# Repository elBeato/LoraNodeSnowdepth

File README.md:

# LoraNodeSnowdepth
A Sensor which measure the snowlevel, temperature and the humiditiy. The sensor is build as a Lora node and communicate over LoraLan with an gateway.

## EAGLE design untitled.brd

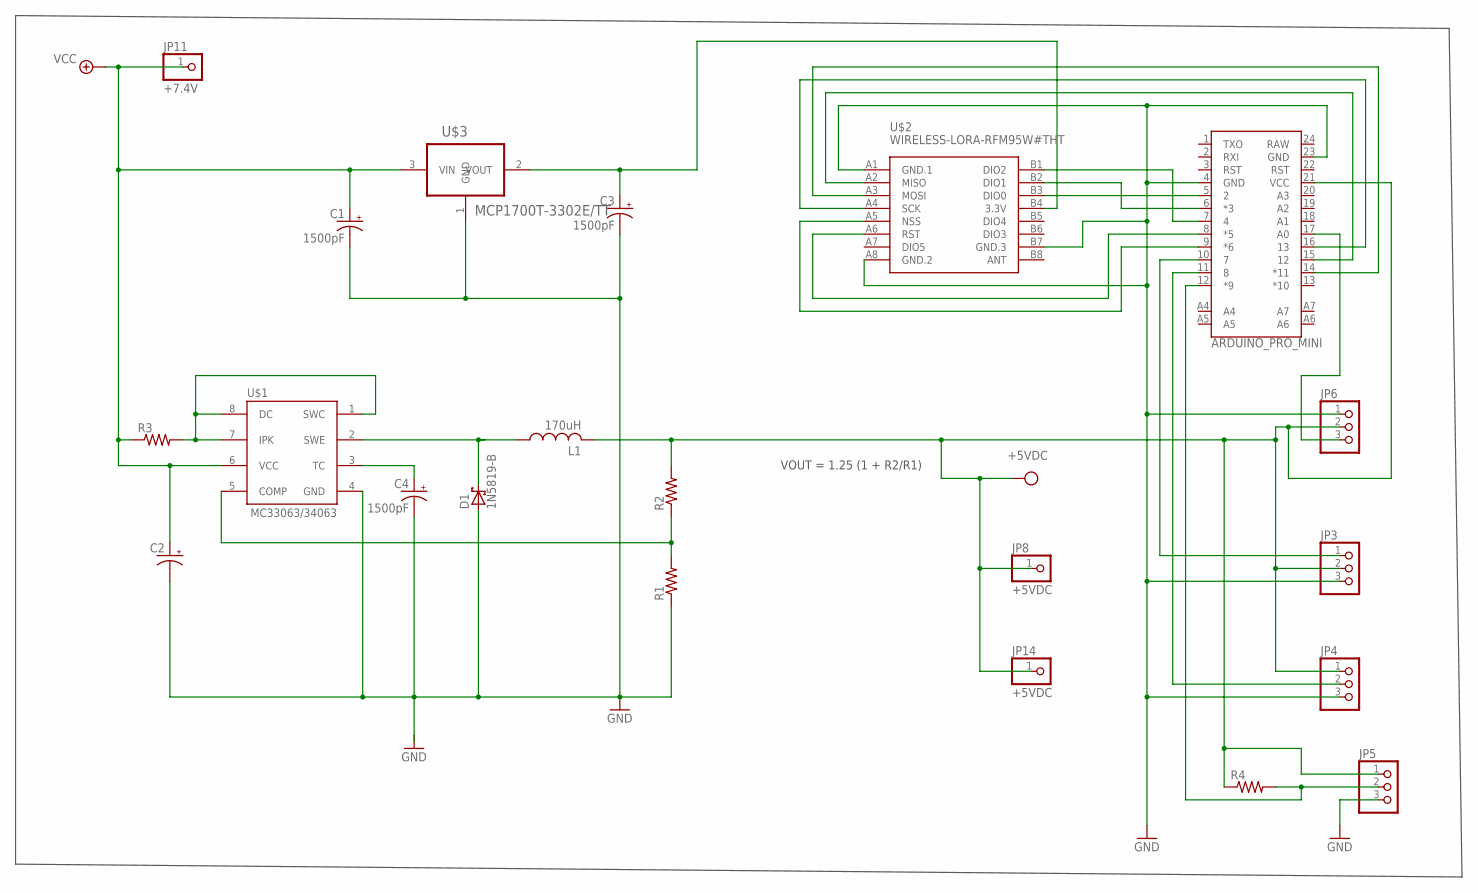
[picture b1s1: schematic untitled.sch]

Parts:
B1: ARDUINO_PRO_MINI
C1, C3, C4: 1500pF; E2,5-6E
C2: 100uF; E2,5-6E
D1: 1N5819-B; DO41-7.6
JP3, JP4, JP5, JP6: PINHD-1X3CB; 1X03-CLEANBIG
JP8, JP14: +5VDC; 1X01
JP11: +7.4V; 1X01
L1: 170uH; 0207/12
R1, R2, R3, R4: R-US_0309/12; 0309/12
U$1: MC33063/MC34063P; DIL08
U$2: WIRELESS-LORA-RFM95W#THT
U$3: MCP1700T-3302E/TT; SOT95P237X112-3N

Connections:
+3.3V: C1.+, C2.+, JP11.1, R3.1, U$1.6 (VCC), U$3.3 (VIN)
GND: B1.4 (GND), B1.23 (GND), C1.-, C2.-, C3.-, C4.-, D1.A, JP3.3, JP4.3, JP5.3, JP6.1, R1.1, U$1.4 (GND), U$2.A1 (GND.1), U$2.A8 (GND.2), U$2.B7 (GND.3), U$3.1 (GND)
unnamed: B1.9 (*6), U$2.A5 (NSS)
unnamed: B1.12 (*9), JP5.2, R4.2
unnamed: D1.C, L1.1, U$1.2 (SWE)
unnamed: R3.2, U$1.1 (SWC), U$1.7 (IPK), U$1.8 (DC)
unnamed: B1.7 (4), U$2.B1 (DIO2)
unnamed: B1.5 (2), U$2.B3 (DIO0)
unnamed: B1.6 (*3), U$2.B2 (DIO1)
unnamed: B1.8 (*5), U$2.A6 (RST)
unnamed: B1.16 (13), U$2.A4 (SCK)
unnamed: B1.14 (*11), U$2.A3 (MOSI)
unnamed: B1.15 (12), U$2.A2 (MISO)
unnamed: B1.11 (8), JP4.2
unnamed: R1.2, R2.1, U$1.5 (COMP)
unnamed: B1.10 (7), JP3.1
unnamed: B1.17 (A0), JP6.3
unnamed: C3.+, U$2.B4 (3.3V), U$3.2 (VOUT)
unnamed: C4.+, U$1.3 (TC)
RAW: B1.24 (RAW)
VCC: B1.21 (VCC), JP3.2, JP4.1, JP5.1, JP6.2, JP8.1, JP14.1, L1.2, R2.2, R4.1

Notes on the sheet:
VOUT = 1.25 (1 + R2/R1)

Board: 2 copper layers, 21 parts (0 on the bottom side), 20 nets, no tracks yet.

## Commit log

2020-09-23 Add files via upload
    Adruino file
2020-09-23 Add files via upload
    PCB

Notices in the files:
parts and their libraries:
SparkFun-Boards: Licensing: Creative Commons ShareAlike 4.0 International - https://creativecommons.org/licenses/by-sa/4.0
diy-modules: Released under the Creative Commons Attribution 4.0 International License: http://creativecommons.org/licenses/by/4.0
